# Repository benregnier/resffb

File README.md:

# resffb
4hp eurorack resonant filter bank based on Serge ResEQ

This is a compact fixed filter bank using the same frequencies as the lower 10 bands of the Serge Resonant EQ. It also features comb outs at the bottom, and a secondary input for feedback.

## Schematic and PCBs

The [kicad](KiCAD) directory contains the schematic and PCB layout as a KiCad 6 project.

*Please note this design does not include reverse polarity protection, and keyed headers don't fit within the width - please be careful to make sure that your power cable's polarity is correct!*

## Panel

Available in the [panel](Panel) directory as a PDF and an SVG vector file.

## License

[CC BY-SA 4.0](http://creativecommons.org/licenses/by-sa/4.0/)

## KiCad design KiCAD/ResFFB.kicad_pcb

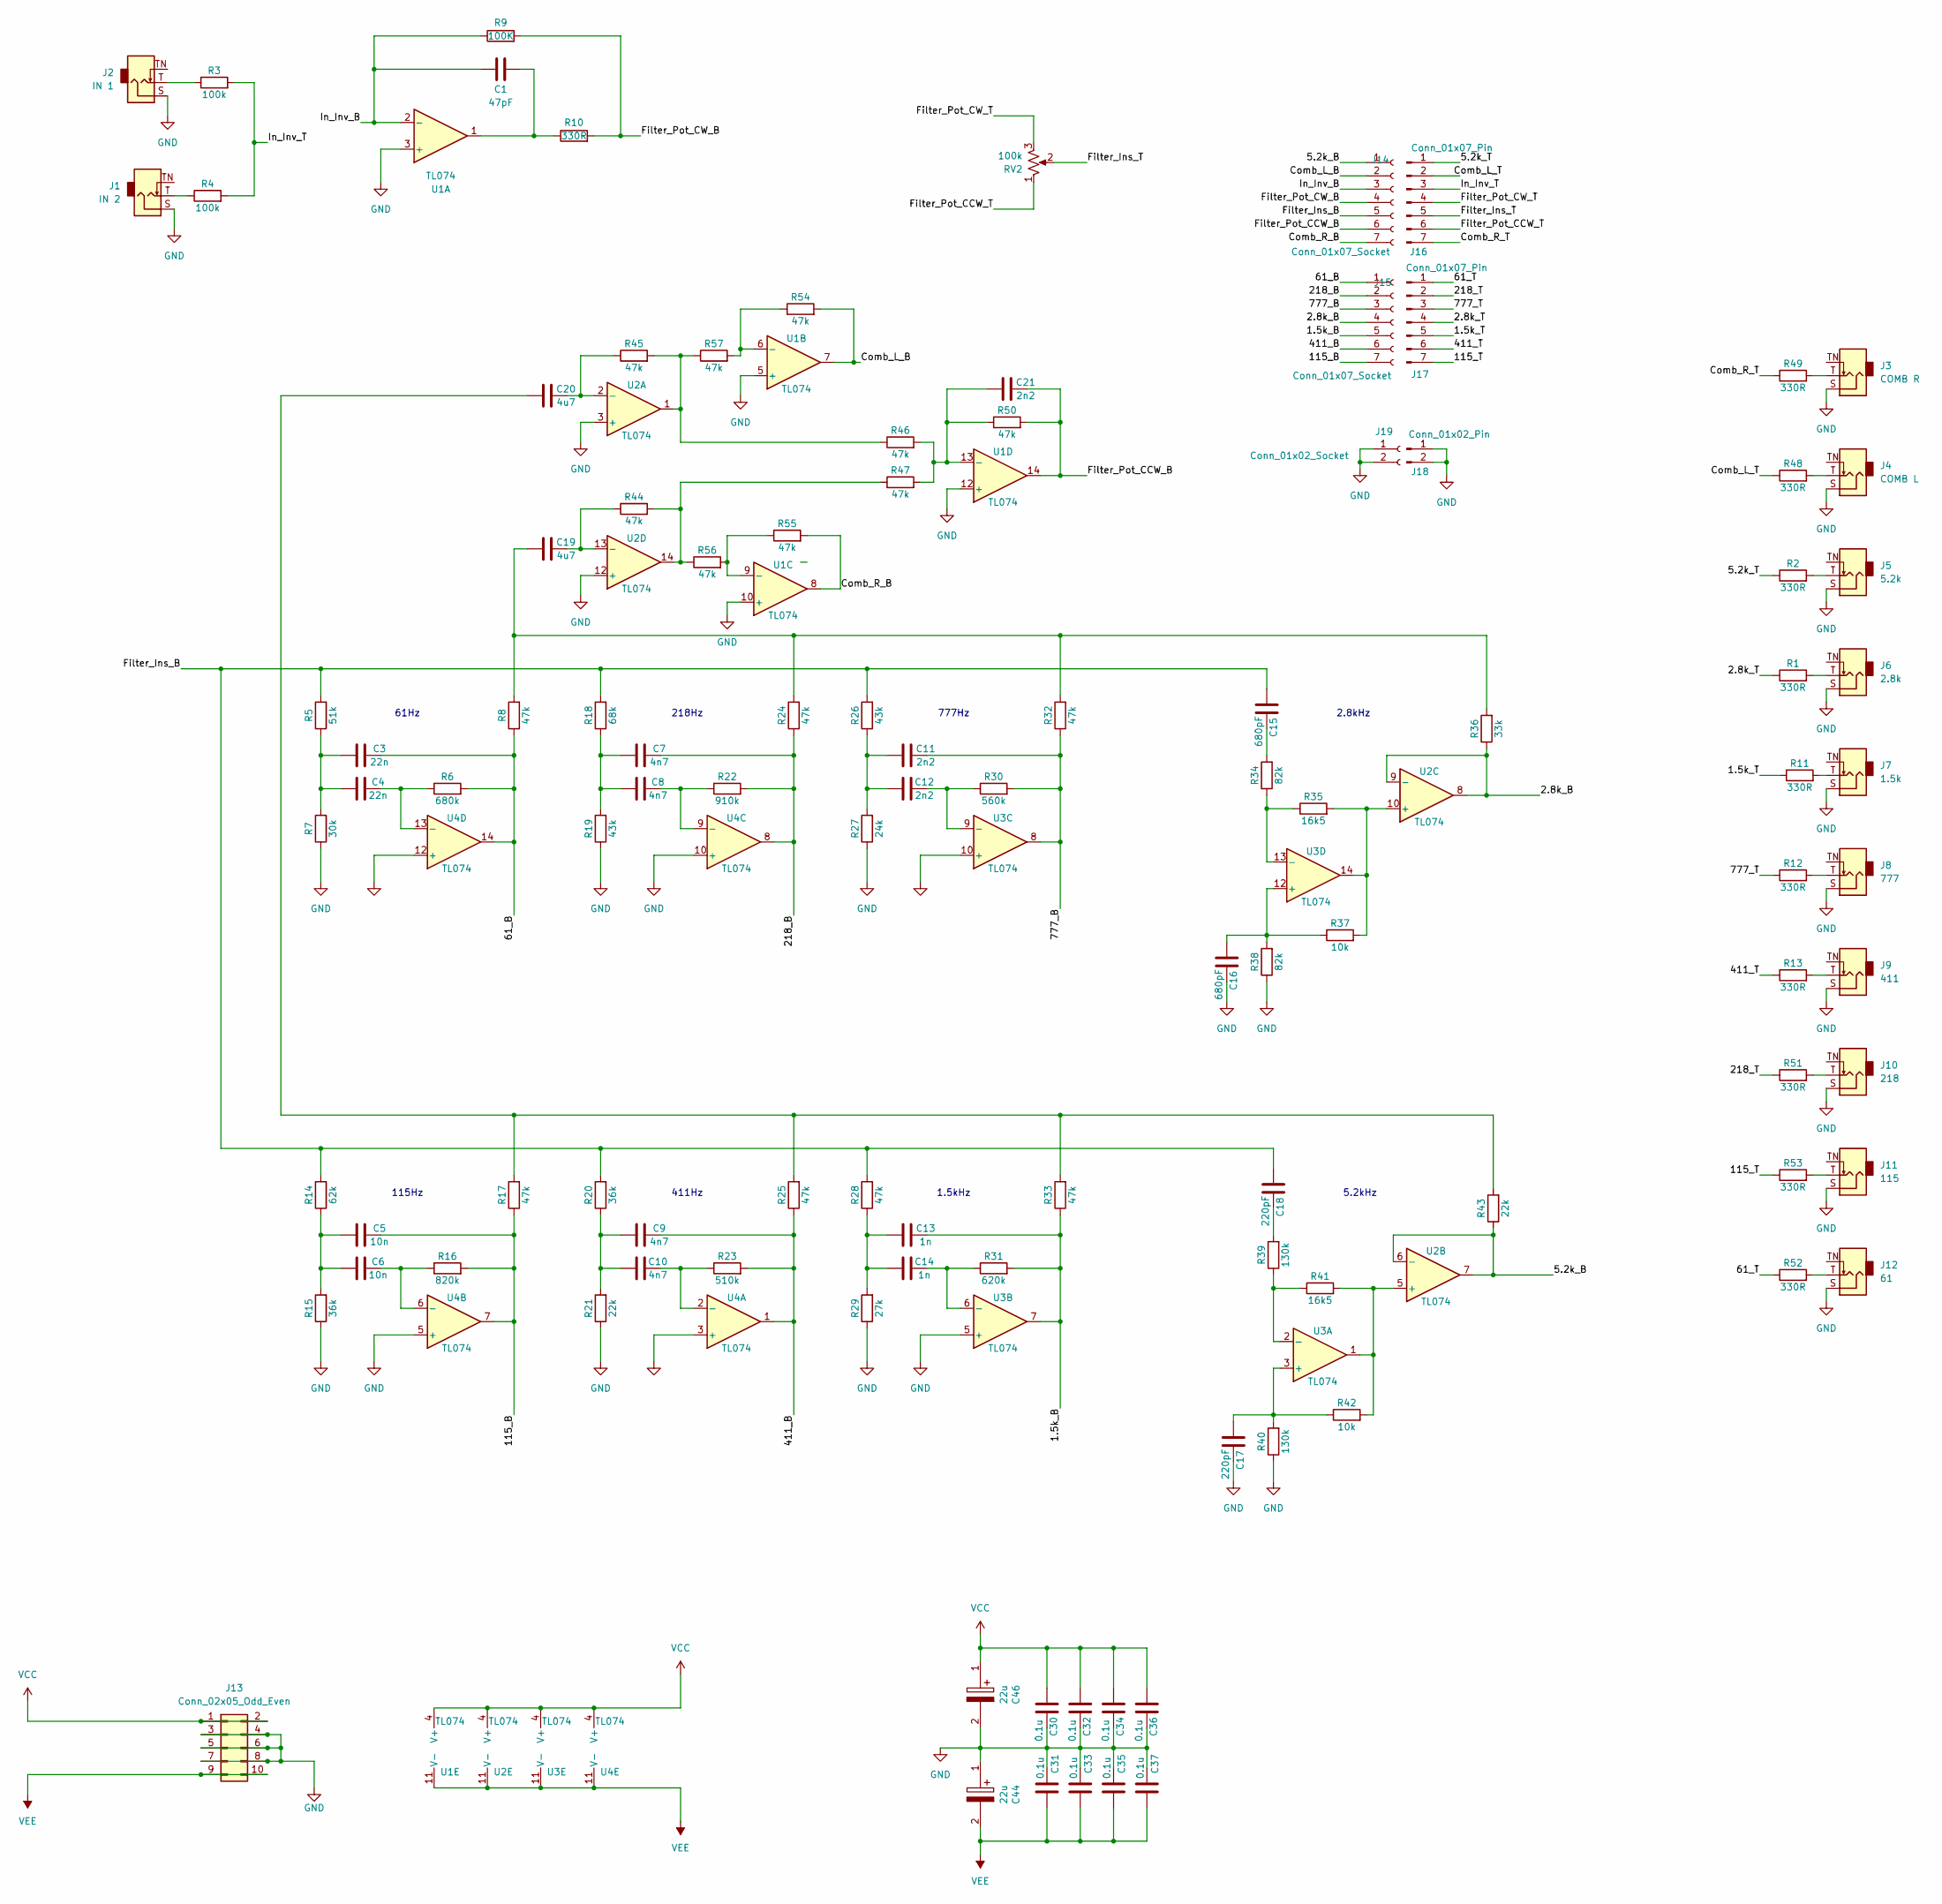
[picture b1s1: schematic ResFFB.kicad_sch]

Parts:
C1: 47pF; C_0805_2012Metric_Pad1.18x1.45mm_HandSolder
C3, C4: 22n; C_0805_2012Metric_Pad1.18x1.45mm_HandSolder
C5, C6: 10n; C_0805_2012Metric_Pad1.18x1.45mm_HandSolder
C7, C8, C9, C10: 4n7; C_0805_2012Metric_Pad1.18x1.45mm_HandSolder
C11, C12, C21: 2n2; C_0805_2012Metric_Pad1.18x1.45mm_HandSolder
C13, C14: 1n; C_0805_2012Metric_Pad1.18x1.45mm_HandSolder
C15, C16: 680pF; C_0805_2012Metric_Pad1.18x1.45mm_HandSolder
C17, C18: 220pF; C_0805_2012Metric_Pad1.18x1.45mm_HandSolder
C19, C20: 4u7; C_Rect_L7.2mm_W8.5mm_P5.00mm_FKP2_FKP2_MKS2_MKP2
C30, C31, C32, C33, C34, C35, C36, C37: 0.1u; C_0805_2012Metric_Pad1.18x1.45mm_HandSolder
C44, C46: 22u; CAPAE430X610N; Manufacturer_Part_Number EEEFN1C220R; Mouser Part Number 667-EEE-FN1A470UR
J1: IN 2; Jack_3.5mm_QingPu_WQP-PJ301M-12_Vertical_Alt
J2: IN 1; Jack_3.5mm_QingPu_WQP-PJ301M-12_Vertical_Alt
J3: COMB R; Jack_3.5mm_QingPu_WQP-PJ301M-12_Vertical_Alt
J4: COMB L; Jack_3.5mm_QingPu_WQP-PJ301M-12_Vertical_Alt
J5: 5.2k; Jack_3.5mm_QingPu_WQP-PJ301M-12_Vertical_Alt
J6: 2.8k; Jack_3.5mm_QingPu_WQP-PJ301M-12_Vertical_Alt
J7: 1.5k; Jack_3.5mm_QingPu_WQP-PJ301M-12_Vertical_Alt
J8: 777; Jack_3.5mm_QingPu_WQP-PJ301M-12_Vertical_Alt
J9: 411; Jack_3.5mm_QingPu_WQP-PJ301M-12_Vertical_Alt
J10: 218; Jack_3.5mm_QingPu_WQP-PJ301M-12_Vertical_Alt
J11: 115; Jack_3.5mm_QingPu_WQP-PJ301M-12_Vertical_Alt
J12: 61; Jack_3.5mm_QingPu_WQP-PJ301M-12_Vertical_Alt
J13: Conn_02x05_Odd_Even; PinHeader_2x05_P2.54mm_Vertical
J14, J15: Conn_01x07_Socket; PinSocket_1x07_P2.54mm_Vertical
J16, J17: Conn_01x07_Pin; PinHeader_1x07_P2.54mm_Vertical
J18: Conn_01x02_Pin; PinHeader_1x02_P2.54mm_Vertical
J19: Conn_01x02_Socket; PinSocket_1x02_P2.54mm_Vertical
R1, R2, R10, R11, R12, R13, R48, R49, R51, R52, R53: 330R; R_0805_2012Metric_Pad1.20x1.40mm_HandSolder
R3, R4: 100k; R_0805_2012Metric_Pad1.20x1.40mm_HandSolder
R5: 51k; R_0805_2012Metric_Pad1.20x1.40mm_HandSolder
R6: 680k; R_0805_2012Metric_Pad1.20x1.40mm_HandSolder
R7: 30k; R_0805_2012Metric_Pad1.20x1.40mm_HandSolder
R8, R17, R24, R25, R28, R32, R33, R44, R45, R46, R47, R50, R54, R55, R56, R57: 47k; R_0805_2012Metric_Pad1.20x1.40mm_HandSolder
R9: 100K; R_0805_2012Metric_Pad1.20x1.40mm_HandSolder
R14: 62k; R_0805_2012Metric_Pad1.20x1.40mm_HandSolder
R15, R20: 36k; R_0805_2012Metric_Pad1.20x1.40mm_HandSolder
R16: 820k; R_0805_2012Metric_Pad1.20x1.40mm_HandSolder
R18: 68k; R_0805_2012Metric_Pad1.20x1.40mm_HandSolder
R19, R26: 43k; R_0805_2012Metric_Pad1.20x1.40mm_HandSolder
R21, R43: 22k; R_0805_2012Metric_Pad1.20x1.40mm_HandSolder
R22: 910k; R_0805_2012Metric_Pad1.20x1.40mm_HandSolder
R23: 510k; R_0805_2012Metric_Pad1.20x1.40mm_HandSolder
R27: 24k; R_0805_2012Metric_Pad1.20x1.40mm_HandSolder
R29: 27k; R_0805_2012Metric_Pad1.20x1.40mm_HandSolder
R30: 560k; R_0805_2012Metric_Pad1.20x1.40mm_HandSolder
R31: 620k; R_0805_2012Metric_Pad1.20x1.40mm_HandSolder
R34, R38: 82k; R_0805_2012Metric_Pad1.20x1.40mm_HandSolder
R35, R41: 16k5; R_0805_2012Metric_Pad1.20x1.40mm_HandSolder
R36: 33k; R_0805_2012Metric_Pad1.20x1.40mm_HandSolder
R37, R42: 10k; R_0805_2012Metric_Pad1.20x1.40mm_HandSolder
R39, R40: 130k; R_0805_2012Metric_Pad1.20x1.40mm_HandSolder
RV2: 100k; Potentiometer_Alpha_RD901F-40-00D_Single_Vertical
U1, U2, U3, U4: TL074; SOIC-14_3.9x8.7mm_P1.27mm

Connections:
/1.5k_B: C13.2, J15.5, R31.2, R33.1, U3.7
/1.5k_T: J17.5, R11.1
/2.8k_B: J15.4, R36.1, U2.8, U2.9 (-)
/2.8k_T: J17.4, R1.1
/5.2k_B: J14.1, R43.1, U2.6 (-), U2.7
/5.2k_T: J16.1, R2.1
/61_B: C3.2, J15.1, R6.2, R8.1, U4.14
/61_T: J17.1, R52.1
/115_B: C5.2, J15.7, R16.2, R17.1, U4.7
/115_T: J17.7, R53.1
/218_B: C7.2, J15.2, R22.2, R24.1, U4.8
/218_T: J17.2, R51.1
/411_B: C9.2, J15.6, R23.2, R25.1, U4.1
/411_T: J17.6, R13.1
/777_B: C11.2, J15.3, R30.2, R32.1, U3.8
/777_T: J17.3, R12.1
/Comb_L_B: J14.2, R54.2, U1.7
/Comb_L_T: J16.2, R48.1
/Comb_R_B: J14.7, R55.2, U1.8
/Comb_R_T: J16.7, R49.1
/Filter_Ins_B: C15.1, C18.1, J14.5, R5.2, R14.2, R18.2, R20.2, R26.2, R28.2
/Filter_Ins_T: J16.5, RV2.2
/Filter_Pot_CCW_B: C21.2, J14.6, R50.2, U1.14
/Filter_Pot_CCW_T: J16.6, RV2.1
/Filter_Pot_CW_B: J14.4, R9.2, R10.2
/Filter_Pot_CW_T: J16.4, RV2.3
/In_Inv_B: C1.1, J14.3, R9.1, U1.2 (-)
/In_Inv_T: J16.3, R3.2, R4.2
GND: C16.2, C17.2, C30.2, C31.1, C32.2, C33.1, C34.2, C35.1, C36.2, C37.1, C44.1, C46.2, J1.S, J2.S, J3.S, J4.S, J5.S, J6.S, J7.S, J8.S, J9.S, J10.S, J11.S, J12.S, J13.3, J13.4, J13.5, J13.6, J13.7, J13.8, J18.1, J18.2, J19.1, J19.2, R7.1, R15.1, R19.1, R21.1, R27.1, R29.1, R38.1, R40.1, U1.3 (+), U1.5 (+), U1.10 (+), U1.12 (+), U2.3 (+), U2.12 (+), U3.5 (+), U3.10 (+), U4.3 (+), U4.5 (+), U4.10 (+), U4.12 (+)
unnamed: C1.2, R10.1, U1.1
unnamed: C3.1, C4.1, R5.1, R7.2
unnamed: C5.1, C6.1, R14.1, R15.2
unnamed: C7.1, C8.1, R18.1, R19.2
unnamed: C9.1, C10.1, R20.1, R21.2
unnamed: C11.1, C12.1, R26.1, R27.2
unnamed: C13.1, C14.1, R28.1, R29.2
unnamed: C15.2, R34.2
unnamed: C18.2, R39.2
unnamed: C19.1, R8.2, R24.2, R32.2, R36.2
unnamed: C20.1, R17.2, R25.2, R33.2, R43.2
unnamed: J1.T, R4.1
unnamed: J2.T, R3.1
unnamed: J3.T, R49.2
unnamed: J4.T, R48.2
unnamed: J5.T, R2.2
unnamed: J6.T, R1.2
unnamed: J7.T, R11.2
unnamed: J8.T, R12.2
unnamed: J9.T, R13.2
unnamed: J10.T, R51.2
unnamed: J11.T, R53.2
unnamed: J12.T, R52.2
unnamed: R44.2, R47.1, R56.1, U2.14
unnamed: R45.2, R46.1, R57.1, U2.1
unnamed: R54.1, R57.2, U1.6 (-)
unnamed: R55.1, R56.2, U1.9 (-)
unnamed: C21.1, R46.2, R47.2, R50.1, U1.13 (-)
unnamed: C20.2, R45.1, U2.2 (-)
unnamed: R41.2, R42.2, U2.5 (+), U3.1
unnamed: R35.2, R37.2, U2.10 (+), U3.14
unnamed: C19.2, R44.1, U2.13 (-)
unnamed: C17.1, R40.2, R42.1, U3.3 (+)
unnamed: R39.1, R41.1, U3.2 (-)
unnamed: C14.2, R31.1, U3.6 (-)
unnamed: C12.2, R30.1, U3.9 (-)
unnamed: C16.1, R37.1, R38.2, U3.12 (+)
unnamed: R34.1, R35.1, U3.13 (-)
unnamed: C10.2, R23.1, U4.2 (-)
unnamed: C6.2, R16.1, U4.6 (-)
unnamed: C8.2, R22.1, U4.9 (-)
unnamed: C4.2, R6.1, U4.13 (-)
VCC: C30.1, C32.1, C34.1, C36.1, C46.1, J13.1, J13.2, U1.4 (V+), U2.4 (V+), U3.4 (V+), U4.4 (V+)
VEE: C31.2, C33.2, C35.2, C37.2, C44.2, J13.9, J13.10, U1.11 (V-), U2.11 (V-), U3.11 (V-), U4.11 (V-)

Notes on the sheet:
2.8kHz
61Hz
411Hz
1.5kHz
115Hz
5.2kHz
777Hz
218Hz

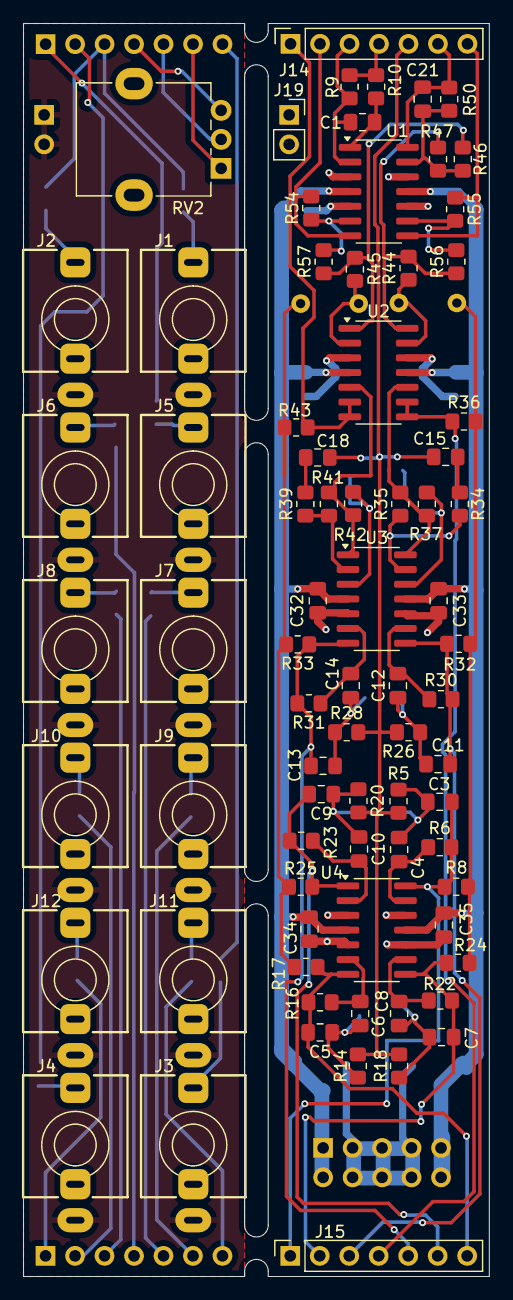
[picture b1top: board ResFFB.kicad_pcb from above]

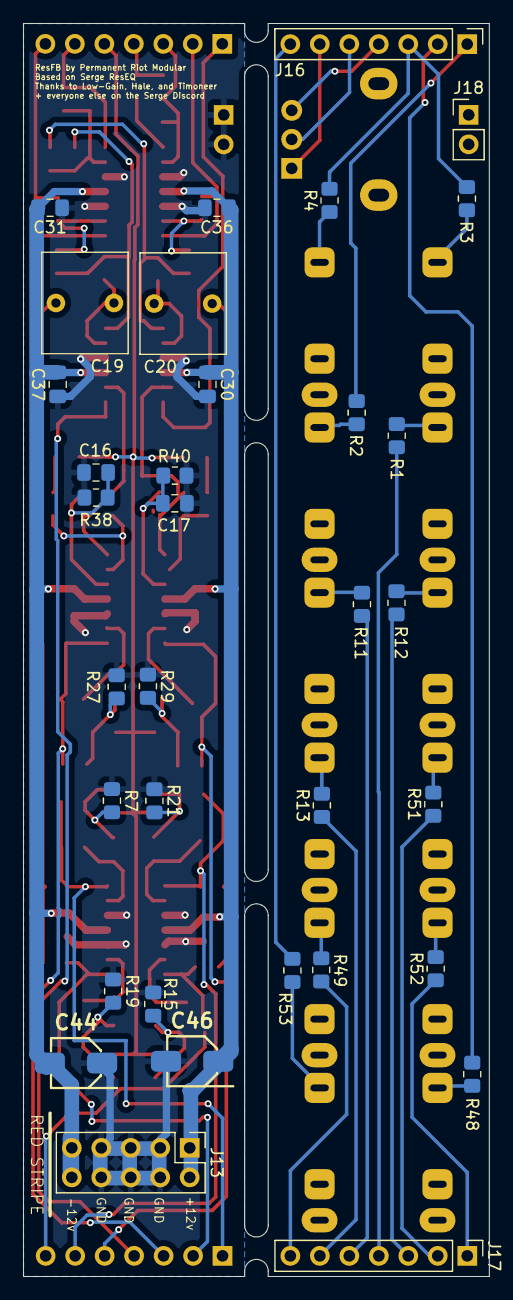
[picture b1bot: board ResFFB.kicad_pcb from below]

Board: 2 copper layers, 40.1 x 108.0 mm, 111 parts (34 on the bottom side), 73 nets.

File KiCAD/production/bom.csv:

Designator,Footprint,Quantity,Value,LCSC Part #
C1,0805,1,47pF,
"C10, C7, C8, C9",0805,4,4n7,
"C11, C12, C21",0805,3,2n2,
"C13, C14",0805,2,1n,
"C15, C16",0805,2,680pF,
"C17, C18",0805,2,220pF,
"C19, C20",C_Rect_L7.2mm_W8.5mm_P5.00mm_FKP2_FKP2_MKS2_MKP2,2,4u7,
"C3, C4",0805,2,22n,
"C30, C31, C32, C33, C34, C35, C36, C37",0805,8,0.1u,
"C44, C46",CAPAE430X610N,2,22u,
"C5, C6",0805,2,10n,
J1,Jack_3.5mm_QingPu_WQP-PJ301M-12_Vertical_Alt,1,IN 2,
J10,Jack_3.5mm_QingPu_WQP-PJ301M-12_Vertical_Alt,1,218,
J11,Jack_3.5mm_QingPu_WQP-PJ301M-12_Vertical_Alt,1,115,
J12,Jack_3.5mm_QingPu_WQP-PJ301M-12_Vertical_Alt,1,61,
J13,PinHeader_2x05_P2.54mm_Vertical,1,Conn_02x05_Odd_Even,
"J14, J15",PinSocket_1x07_P2.54mm_Vertical,2,Conn_01x07_Socket,
"J16, J17",PinHeader_1x07_P2.54mm_Vertical,2,Conn_01x07_Pin,
J18,PinHeader_1x02_P2.54mm_Vertical,1,Conn_01x02_Pin,
J19,PinSocket_1x02_P2.54mm_Vertical,1,Conn_01x02_Socket,
J2,Jack_3.5mm_QingPu_WQP-PJ301M-12_Vertical_Alt,1,IN 1,
J3,Jack_3.5mm_QingPu_WQP-PJ301M-12_Vertical_Alt,1,COMB R,
J4,Jack_3.5mm_QingPu_WQP-PJ301M-12_Vertical_Alt,1,COMB L,
J5,Jack_3.5mm_QingPu_WQP-PJ301M-12_Vertical_Alt,1,5.2k,
J6,Jack_3.5mm_QingPu_WQP-PJ301M-12_Vertical_Alt,1,2.8k,
J7,Jack_3.5mm_QingPu_WQP-PJ301M-12_Vertical_Alt,1,1.5k,
J8,Jack_3.5mm_QingPu_WQP-PJ301M-12_Vertical_Alt,1,777,
J9,Jack_3.5mm_QingPu_WQP-PJ301M-12_Vertical_Alt,1,411,
"R1, R10, R11, R12, R13, R2, R48, R49, R51, R52, R53",0805,11,330R,
R14,0805,1,62k,
"R15, R20",0805,2,36k,
R16,0805,1,820k,
"R17, R24, R25, R28, R32, R33, R44, R45, R46, R47, R50, R54, R55, R56, R57, R8",0805,16,47k,
R18,0805,1,68k,
"R19, R26",0805,2,43k,
"R21, R43",0805,2,22k,
R22,0805,1,910k,
R23,0805,1,510k,
R27,0805,1,24k,
R29,0805,1,27k,
"R3, R4, R9",0805,3,100k,
R30,0805,1,560k,
R31,0805,1,620k,
"R34, R38",0805,2,82k,
"R35, R41",0805,2,16k5,
R36,0805,1,33k,
"R37, R42",0805,2,10k,
"R39, R40",0805,2,130k,
R5,0805,1,51k,
R6,0805,1,680k,
R7,0805,1,30k,
RV2,Potentiometer_Alpha_RD901F-40-00D_Single_Vertical,1,100k,
"U1, U2, U3, U4",SOIC-14_3.9x8.7mm_P1.27mm,4,TL074,

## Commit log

2025-07-19 Gerber Update
2025-07-19 Added Images
2025-07-19 Rename 20250719_210915740_iOS.jpg to front.jpg
    changed names
2025-07-19 Rename 20250719_210923852_iOS.jpg to side.jpg
2025-07-19 Added Images again
2025-07-19 extra file removal
2025-07-19 BOM fix
